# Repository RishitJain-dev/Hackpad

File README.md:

# **Hackpad**
  A custom 6-key mechanical Macropad with rotary encoder, OLED screen and fully programmable shortcuts for your workflow.

  ## 1. Designing the macropad - 20 minutes
   I used Figma to create initial designs before designing the PCB and schematic  

 ## 2. Designing the schematic - 30 minutes
 
 ### Components:  
   -ER_OLEDM0.91_1x-I2C  
   -RotaryEncoder_Switch_MP  
   -XIAO_ESP32C3  
   -Cherry MX Switches  
   -1N4001 Diode   

 ## 3. Designing the PCB - 1 hour 30 minutes
   I used KiCad to design the PCB, routing traces, and linking 3D models to each footprint to create a final 3D render of the PCB

## 4. Designing the CAD - 1 hour 18 minutes
   I used Onshape to design the CAD, splitting the casing into 3 pieces, the body, top and bottom, all connected by nuts and bolts, and keycaps for the switches and a knob for the rotary encoder

# Bill of Materials
6x Cherry MX Switches

6x Keycaps any colour (preferably black)

1x EC11 Rotary Encoder with switch and MP pins

1x Seeed XIAO RP2040

4x M3 Nut and Bolt, 2cm, Low profile top

4x M3 Spacers, 3mm diameter, 0.6cm, circular, non-threaded

1 Case (3 printed parts)

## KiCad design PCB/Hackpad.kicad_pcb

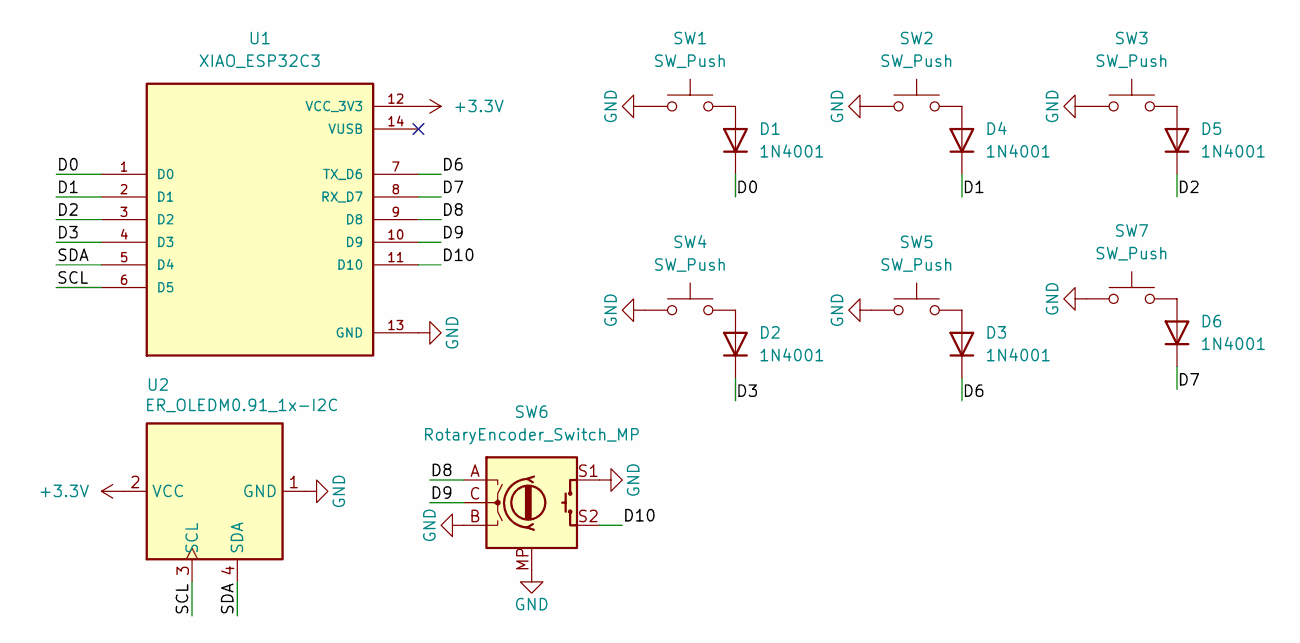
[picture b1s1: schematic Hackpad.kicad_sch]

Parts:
D1, D2, D3, D4, D5, D6: 1N4001; D_DO-41_SOD81_P10.16mm_Horizontal
SW1, SW2, SW3, SW4, SW5, SW7: SW_Push; SW_Cherry_MX_1.00u_Plate
SW6: RotaryEncoder_Switch_MP; RotaryEncoder_Alps_EC11E-Switch_Vertical_H20mm_CircularMoun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
U1: XIAO_ESP32C3; MODULE_XIAO_ESP32C3; PARTREV 23/05/2022
U2: ER_OLEDM0.91_1x-I2C

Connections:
+3.3V: U1.12 (VCC_3V3), U2.2 (VCC)
/D0: D1.1 (K), U1.1 (D0)
/D1: D4.1 (K), U1.2 (D1)
/D2: D5.1 (K), U1.3 (D2)
/D3: D2.1 (K), U1.4 (D3)
/D6: D3.1 (K), U1.7 (TX_D6)
/D7: D6.1 (K), U1.8 (RX_D7)
/D8: SW6.A, U1.9 (D8)
/D9: SW6.C, U1.10 (D9)
/D10: SW6.S2, U1.11 (D10)
/SCL: U1.6 (D5), U2.3 (SCL)
/SDA: U1.5 (D4), U2.4 (SDA)
GND: SW1.1, SW2.1, SW3.1, SW4.1, SW5.1, SW6.B, SW6.MP, SW6.S1, SW7.1, U1.13 (GND), U2.1 (GND)
unnamed: D1.2 (A), SW1.2
unnamed: D2.2 (A), SW4.2
unnamed: D3.2 (A), SW5.2
unnamed: D4.2 (A), SW2.2
unnamed: D5.2 (A), SW3.2
unnamed: D6.2 (A), SW7.2

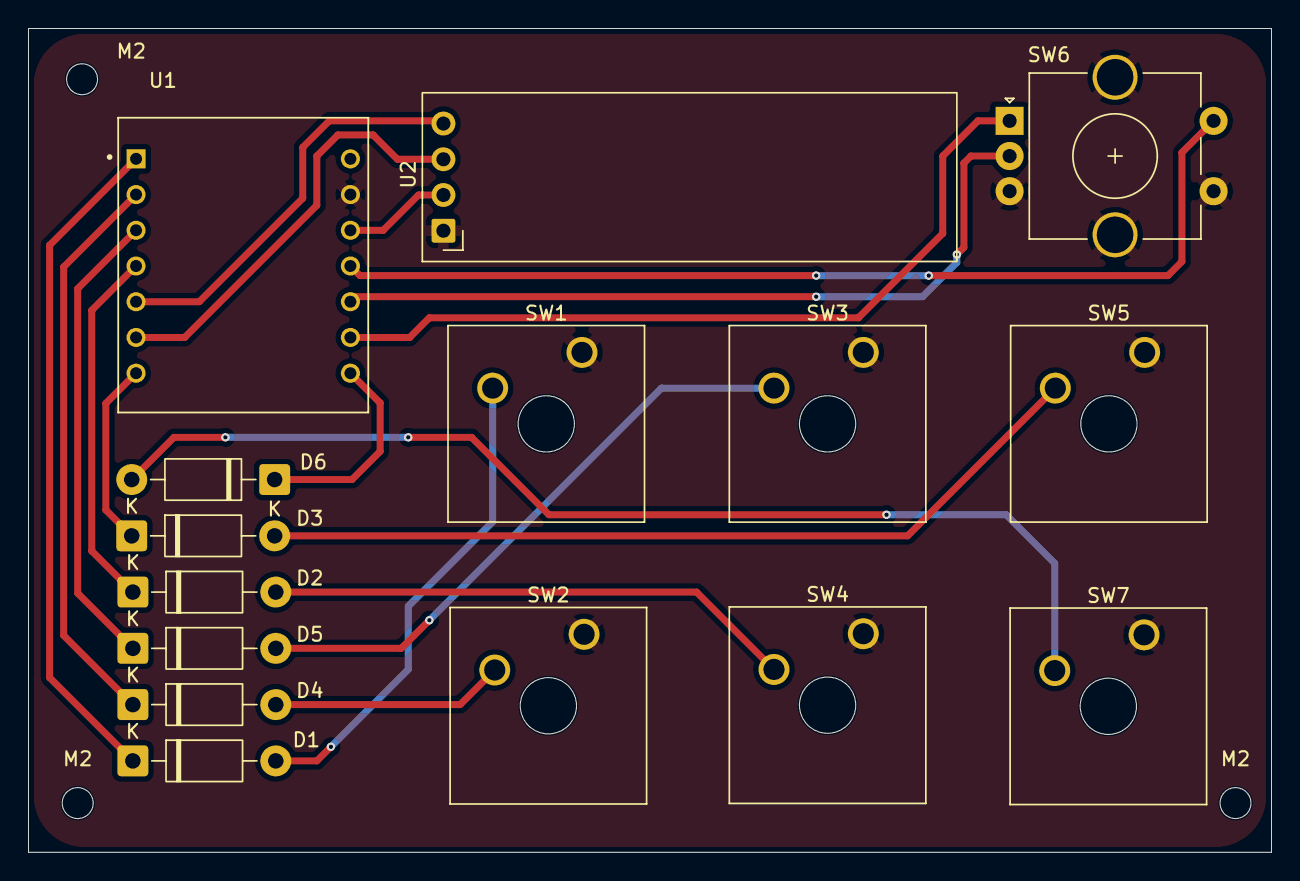
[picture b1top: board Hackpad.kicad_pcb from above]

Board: 2 copper layers, 88.4 x 58.6 mm, 18 parts (0 on the bottom side), 19 nets.

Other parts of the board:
M2, M2#2, M2#3: MountingHole_2.2mm_M2

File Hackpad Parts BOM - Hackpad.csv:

,Designator,Footprint,Quantity,Designation,Supplier and ref,cost
1,"D1, D2, D3, D4, D5, D6",D_DO-41_SOD81_P10.16mm_Horizontal,6,1N4001,,0
2,"SW1, SW2, SW3, SW4, SW5, SW7",SW_Cherry_MX_1.00u_Plate,6,SW_Push,,0
3,SW6,RotaryEncoder_Alps_EC11E-Switch_Vertical_H20mm_CircularMountingHoles,1,RotaryEncoder_Switch_MP,,0
4,U1,MODULE_XIAO_ESP32C3,1,XIAO_ESP32C3,,0
5,U2,ER_OLEDM0.91_1x-I2C,1,ER_OLEDM0.91_1x-I2C,,0
,,,,,,
,total parts cost:,0 ( all included in the hackpad parts kit.),,,,
